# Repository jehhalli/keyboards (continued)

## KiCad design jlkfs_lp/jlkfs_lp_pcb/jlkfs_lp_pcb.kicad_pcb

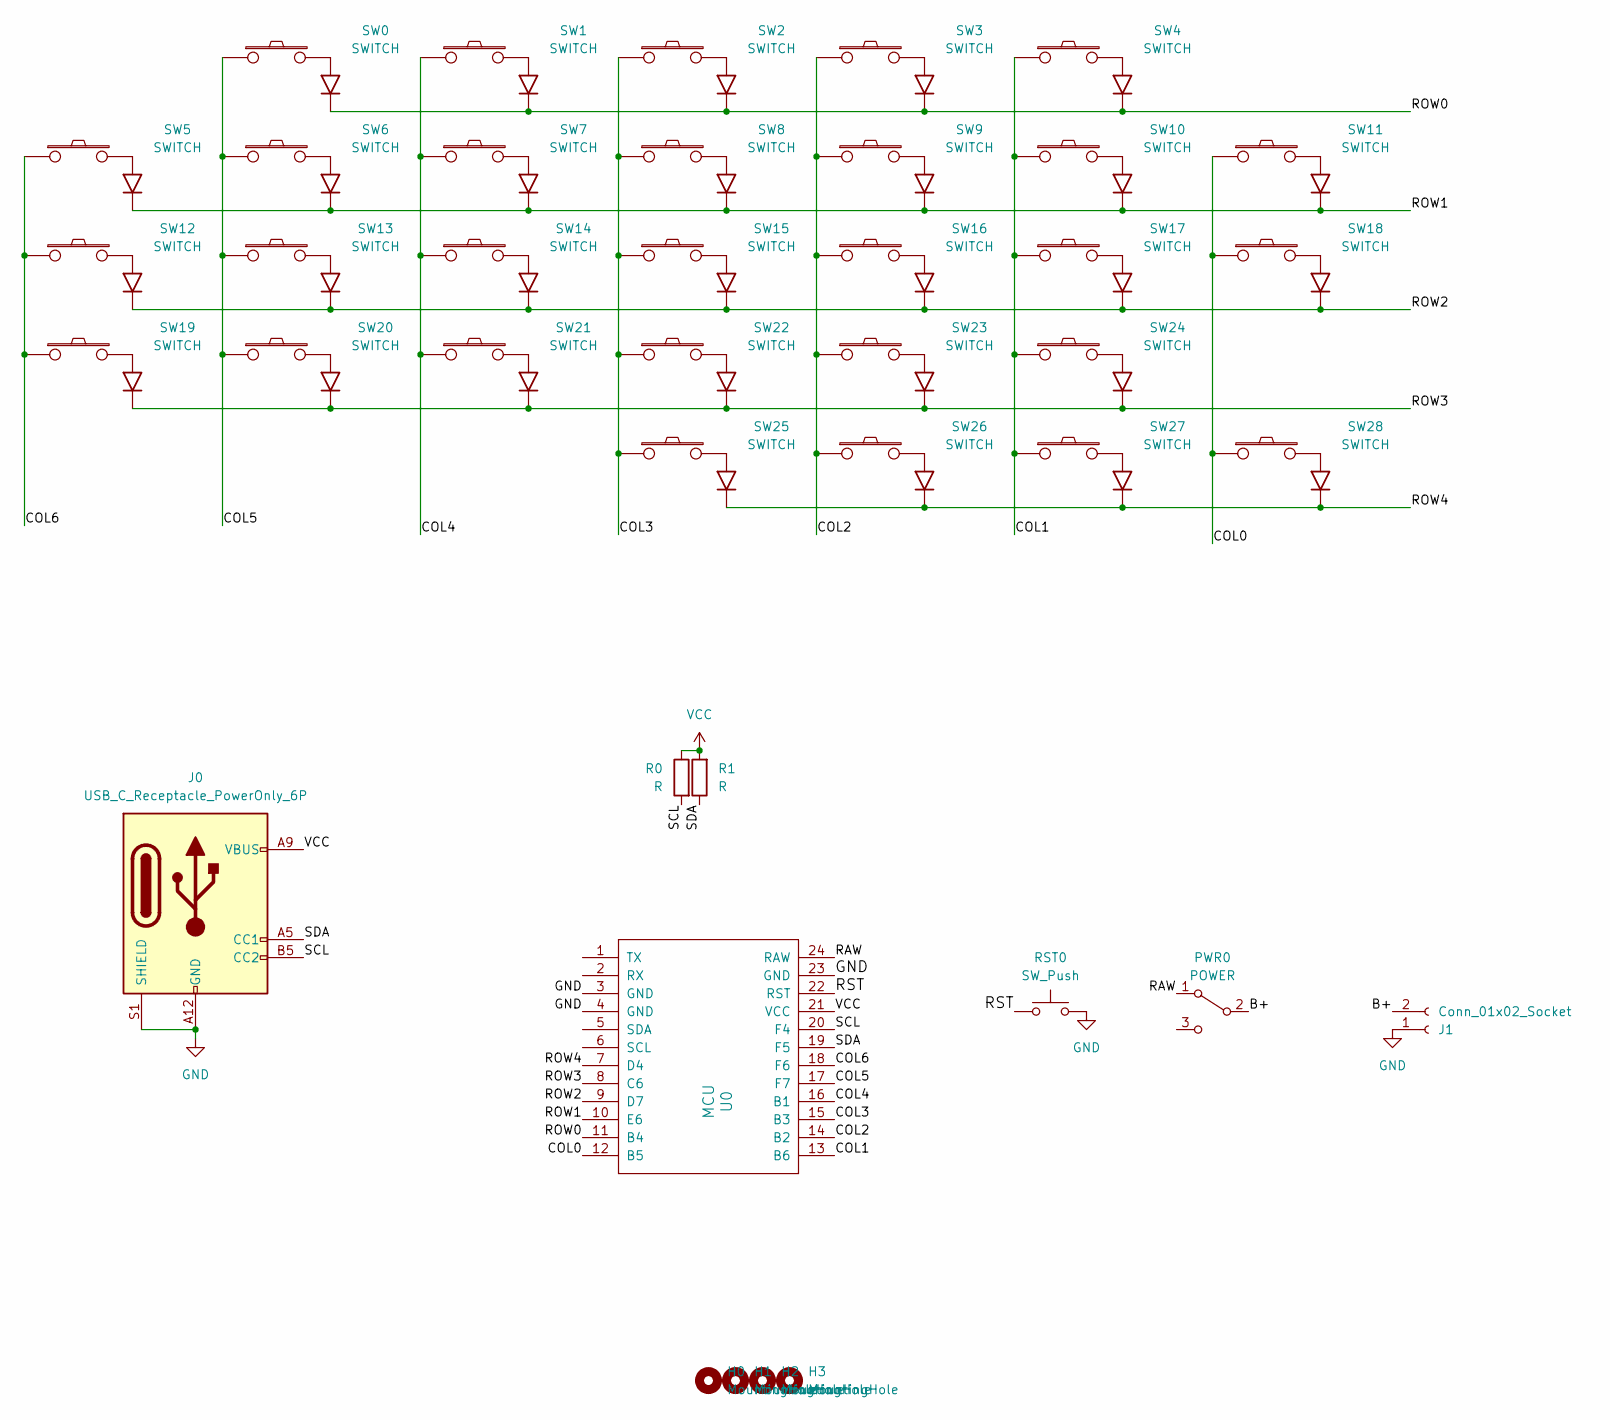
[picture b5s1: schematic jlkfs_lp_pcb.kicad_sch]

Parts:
H0, H1, H2, H3: MountingHole; MountingHole_3.5mm
J0: USB_C_Receptacle_PowerOnly_6P; USB4515
J1: Conn_01x02_Socket; PinHeader_1x02_P2.54mm_Vertical
PWR0: POWER; power_switch_1
R0, R1: R; R_0805_2012Metric_Pad1.20x1.40mm_HandSolder
RST0: SW_Push; reset_button
SW0, SW1, SW2, SW3, SW4, SW5, SW6, SW7, SW8, SW9, SW10, SW11, SW12, SW13, SW14, SW15, SW16, SW17, SW18, SW19, SW20, SW21, SW22, SW23, SW24, SW25, SW26: SWITCH; kailh_choc_dual_with_diode
SW27, SW28: SWITCH; kailh_choc_dual_with_diode_15
U0: MCU; pro_micro_castellated

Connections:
/B+: J1.2, PWR0.2 (B)
/COL0: SW11.1, SW18.1, SW28.1, U0.12 (B5)
/COL1: SW4.1, SW10.1, SW17.1, SW24.1, SW27.1, U0.13 (B6)
/COL2: SW3.1, SW9.1, SW16.1, SW23.1, SW26.1, U0.14 (B2)
/COL3: SW2.1, SW8.1, SW15.1, SW22.1, SW25.1, U0.15 (B3)
/COL4: SW1.1, SW7.1, SW14.1, SW21.1, U0.16 (B1)
/COL5: SW0.1, SW6.1, SW13.1, SW20.1, U0.17 (F7)
/COL6: SW5.1, SW12.1, SW19.1, U0.18 (F6)
/RAW: PWR0.1 (A), U0.24 (RAW)
/ROW0: SW0.3 (K), SW1.3 (K), SW2.3 (K), SW3.3 (K), SW4.3 (K), U0.11 (B4)
/ROW1: SW5.3 (K), SW6.3 (K), SW7.3 (K), SW8.3 (K), SW9.3 (K), SW10.3 (K), SW11.3 (K), U0.10 (E6)
/ROW2: SW12.3 (K), SW13.3 (K), SW14.3 (K), SW15.3 (K), SW16.3 (K), SW17.3 (K), SW18.3 (K), U0.9 (D7)
/ROW3: SW19.3 (K), SW20.3 (K), SW21.3 (K), SW22.3 (K), SW23.3 (K), SW24.3 (K), U0.8 (C6)
/ROW4: SW25.3 (K), SW26.3 (K), SW27.3 (K), SW28.3 (K), U0.7 (D4)
/RST: RST0.1, U0.22 (RST)
/SCL: J0.B5 (CC2), R0.2, U0.20 (F4)
/SDA: J0.A5 (CC1), R1.1, U0.19 (F5)
GND: J0.A12 (GND), J0.B12 (GND), J0.S1 (SHIELD), J1.1, RST0.2, U0.3 (GND), U0.4 (GND), U0.23 (GND)
VCC: J0.A9 (VBUS), J0.B9 (VBUS), R0.1, R1.2, U0.21 (VCC)

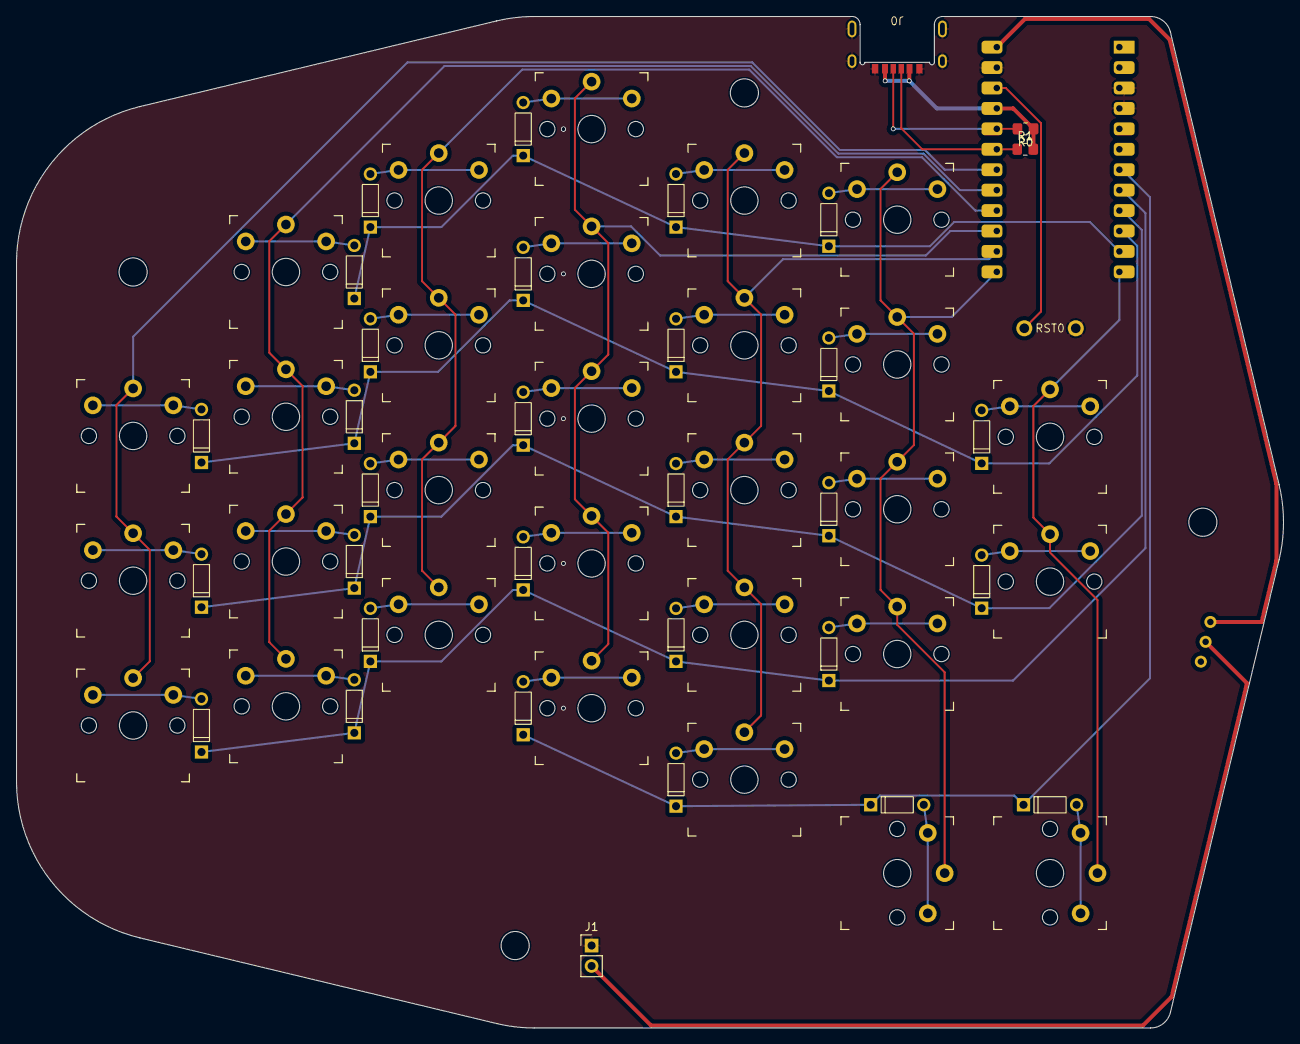
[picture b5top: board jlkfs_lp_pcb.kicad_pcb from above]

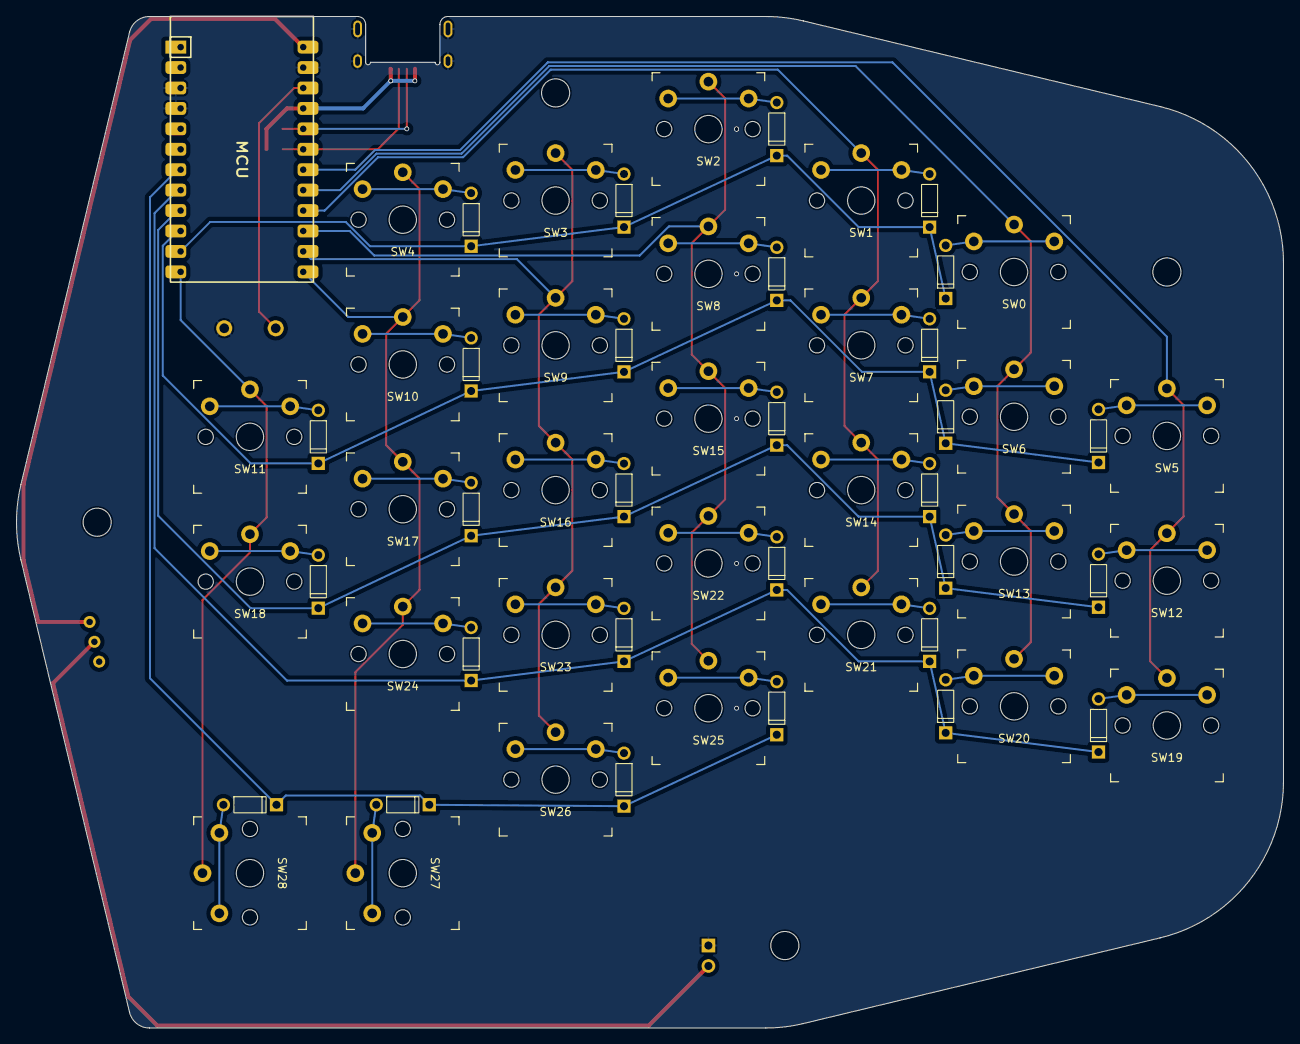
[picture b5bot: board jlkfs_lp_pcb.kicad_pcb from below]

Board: 2 copper layers, 157.5 x 125.8 mm, 40 parts (23 on the bottom side), 19 nets.

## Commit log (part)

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2023-11-27 First commit.
2023-11-27 Renamed the kicad project to jl142.
2023-11-28 Moved libraries around.
2023-11-28 Moved files around.
2023-11-28 Moved again.
2023-12-02 Changed the pro micro symbol.
2023-12-08 Routed rev2 of jl142.
2023-12-19 Renamed jl142 to jlk.
2023-12-19 Added KeysForSuccess.
2023-12-21 Added fillet to cherry plate footprint.
2023-12-21 Final? design of jlk before fillet and creating plates.
2023-12-21 Fillet lines, add tplate, bplate for jlk.
2023-12-21 Updates to kfs.
2023-12-22 Switched to SMD diode, col2row.
2023-12-22 Many updates to kfs. Now low profile.
2023-12-23 Slight mods to kfs.
2023-12-23 Moved some mounting holes on the kfs.
2023-12-23 Switched to staggered kfs layout.
2023-12-23 Moved the bottom row of kfs farther inward.
2023-12-24 Changed the reset button on the jlk.
2023-12-24 Updated reset button and mounting holes on kfs.
2023-12-25 Added back rev1 of jl142.
2023-12-25 Changed reset button again. Removed some standoffs.
2023-12-25 Reverted the cherry hotswap footprint.
2023-12-25 Changed jlk for mounting promicro under the pcb.
2023-12-27 Switched jlk to use nice!nano.
2023-12-27 Switched kfs to use nice!nano.
2023-12-27 Changed the reset and power switches for kfs and jlk.
2023-12-27 Changed the cherry footprint to get rid of silkscreen warnings.
2023-12-27 Slight update to jlk.
2023-12-27 Moved some kfs mounting holes.
2023-12-28 Moved mcu to underside of pcb, added battery jack.
2023-12-28 Added ground connection to power switch chassis.
2023-12-28 Small changes.
2023-12-29 Added filled polygons on top and bottom plates.
2024-01-18 First pass at jlks.
2024-01-18 Changed out the power switch and reset button on jlks.
2024-01-19 Updates to jlks, added corresponding top and bottom plates.
2024-01-19 Refill on jlks pcb.
2024-01-19 Moved bplate rubber pad outlines to copper layers.
2024-01-19 Moved the battery pins and power switch on the jlks.
2024-01-20 Created sun and moon graphics on the jlks top plate.
2024-01-20 Changed sun rays to .15mm thickness.
2024-01-20 Moved some of the mounting holes around.
2024-01-20 Added sun and moon logos to footprints.
2024-01-20 Small modifications to the top and bottom plates.
2024-06-22 Adding a new full split keyboard.
2024-06-23 Routed jlkfs.
2024-06-23 Moved the outside pinky row down slightly.
2024-09-02 Started a low profile jlkfs.
2024-09-05 Adding jlkfs_top and jlkfs_bottom projects.
2024-09-05 Adding a jlkfs_bottom_dual for linking two halves.
2024-09-05 Fixed up the jlkfs bottom plates.
2024-09-07 Updates to jlkfs_lp
2024-09-07 Starting to create upper and lower decks for jlkfs_lp.
2024-09-08 Updated jlkfs_lp.
2024-09-08 Rename.
2024-09-08 Updates to jlkfs_lp.
2024-09-08 Added a battery path for nice!nano to jlkfs.
2026-04-16 Adding stale changes. Not sure what state this is in.
2026-05-22 Removing the jlkfs_lp.
2026-05-22 Creating a new jlkws: jlk wired split.
2026-05-25 Adding jst inter-board connector to jlkws.
2026-05-26 Adding a mostly ortholinear keyboard.
2026-05-26 Adding a top plate for the olk.
2026-05-26 Completed a lot of the per-switch routing on olk.
2026-05-26 Adding missing footprint.
2026-05-26 Adding logo to olk top, and to library.
2026-05-26 Changed the shape of the olk_pcb.
2026-05-26 Altered the JL logo.
2026-05-26 Updated the top shape to match the pcb.
2026-05-27 Changed olk to more ortholinear grid.
2026-05-29 Routed the olk.
2026-05-29 Switching olk to castellated pro micro footprint.
2026-05-29 Moved the keys around again on olk.
2026-05-29 Updated olk_top to match the new layout.
2026-05-29 Adding a bottom plate for olk.
2026-05-29 Fillet olk pcb outline.
2026-05-29 Removed soldermask from underside of castellated pro micro.
2026-05-29 Adding option for battery in olk_pcb.
